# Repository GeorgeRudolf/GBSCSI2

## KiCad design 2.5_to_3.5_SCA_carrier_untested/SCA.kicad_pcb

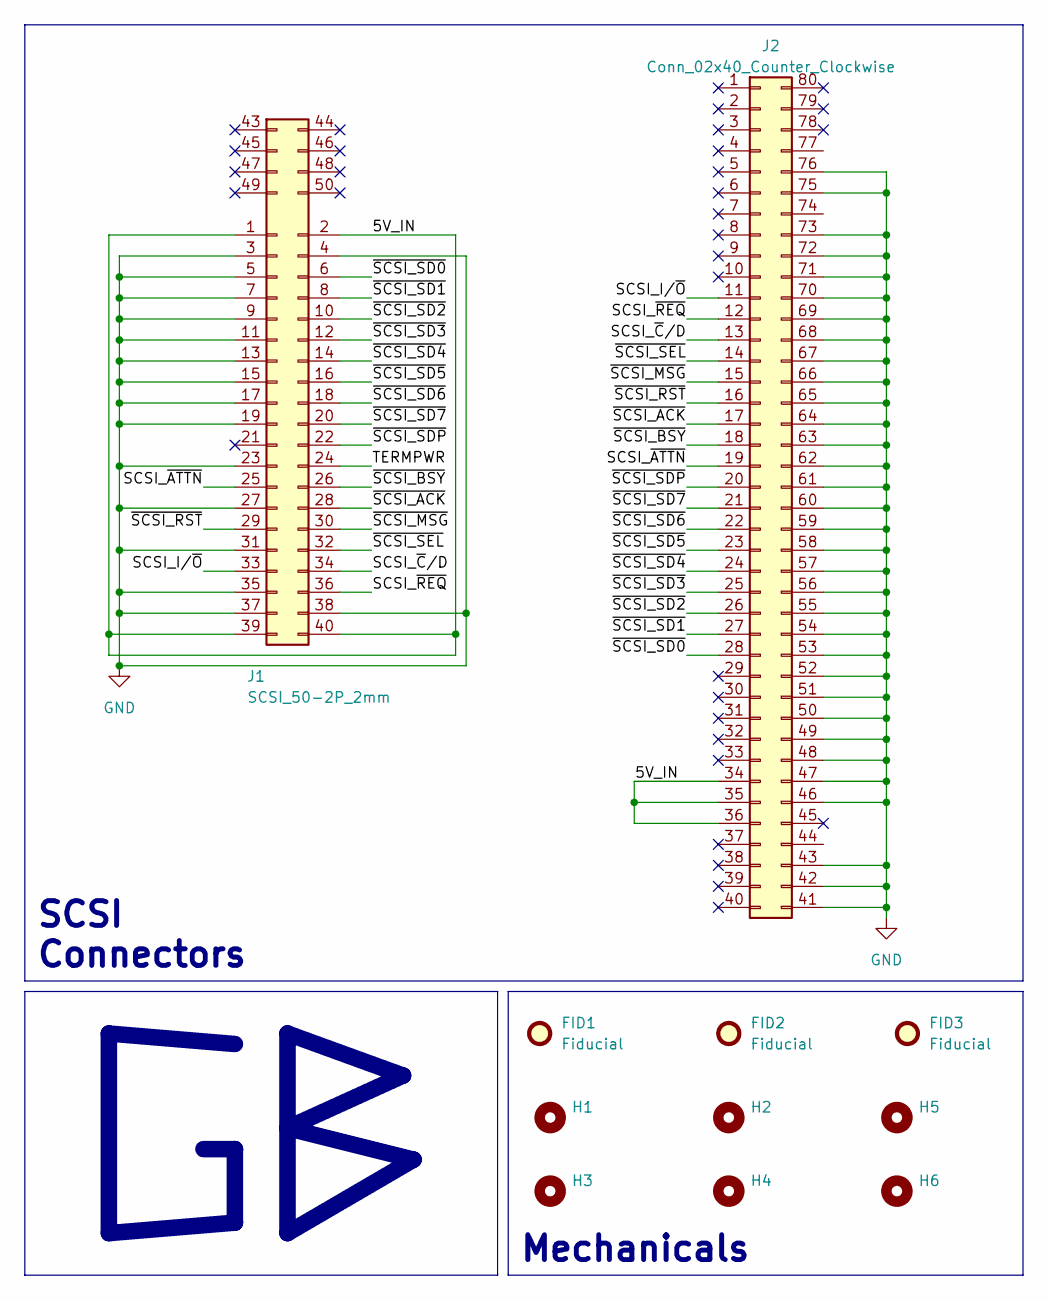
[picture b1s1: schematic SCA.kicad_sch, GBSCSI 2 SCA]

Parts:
FID1, FID2, FID3: Fiducial; Fiducial_0.5mm_Mask1mm; LCSC N/A
H1, H2, H3, H4, H5, H6: MH2.5_NPTH; LCSC N/A
J1: SCSI_50-2P_2mm; PinSocket_2x20_P2.00mm_Horizontal; LCSC N/A
J2: Conn_02x40_Counter_Clockwise; CHAMPII_80

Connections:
/5V_IN: J1.1, J1.2, J1.39, J1.40, J2.34, J2.35, J2.36
/SCSI_I/~O: J1.33, J2.11
/SCSI_~ATTN: J1.25, J2.19
/SCSI_~C/D: J1.34, J2.13
/SCSI_~REQ: J1.36, J2.12
/TERMPWR: J1.24
/~SCSI_ACK: J1.28, J2.17
/~SCSI_BSY: J1.26, J2.18
/~SCSI_MSG: J1.30, J2.15
/~SCSI_RST: J1.29, J2.16
/~SCSI_SD0: J1.6, J2.28
/~SCSI_SD1: J1.8, J2.27
/~SCSI_SD2: J1.10, J2.26
/~SCSI_SD3: J1.12, J2.25
/~SCSI_SD4: J1.14, J2.24
/~SCSI_SD5: J1.16, J2.23
/~SCSI_SD6: J1.18, J2.22
/~SCSI_SD7: J1.20, J2.21
/~SCSI_SDP: J1.22, J2.20
/~SCSI_SEL: J1.32, J2.14
GND: J1.3, J1.4, J1.5, J1.7, J1.9, J1.11, J1.13, J1.15, J1.17, J1.19, J1.23, J1.27, J1.31, J1.35, J1.37, J1.38, J2.41, J2.42, J2.43, J2.46, J2.47, J2.48, J2.49, J2.50, J2.51, J2.52, J2.53, J2.54, J2.55, J2.56, J2.57, J2.58, J2.59, J2.60, J2.61, J2.62, J2.63, J2.64, J2.65, J2.66, J2.67, J2.68, J2.69, J2.70, J2.71, J2.72, J2.73, J2.75, J2.76

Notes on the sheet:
SCSI Connectors
Mechanicals

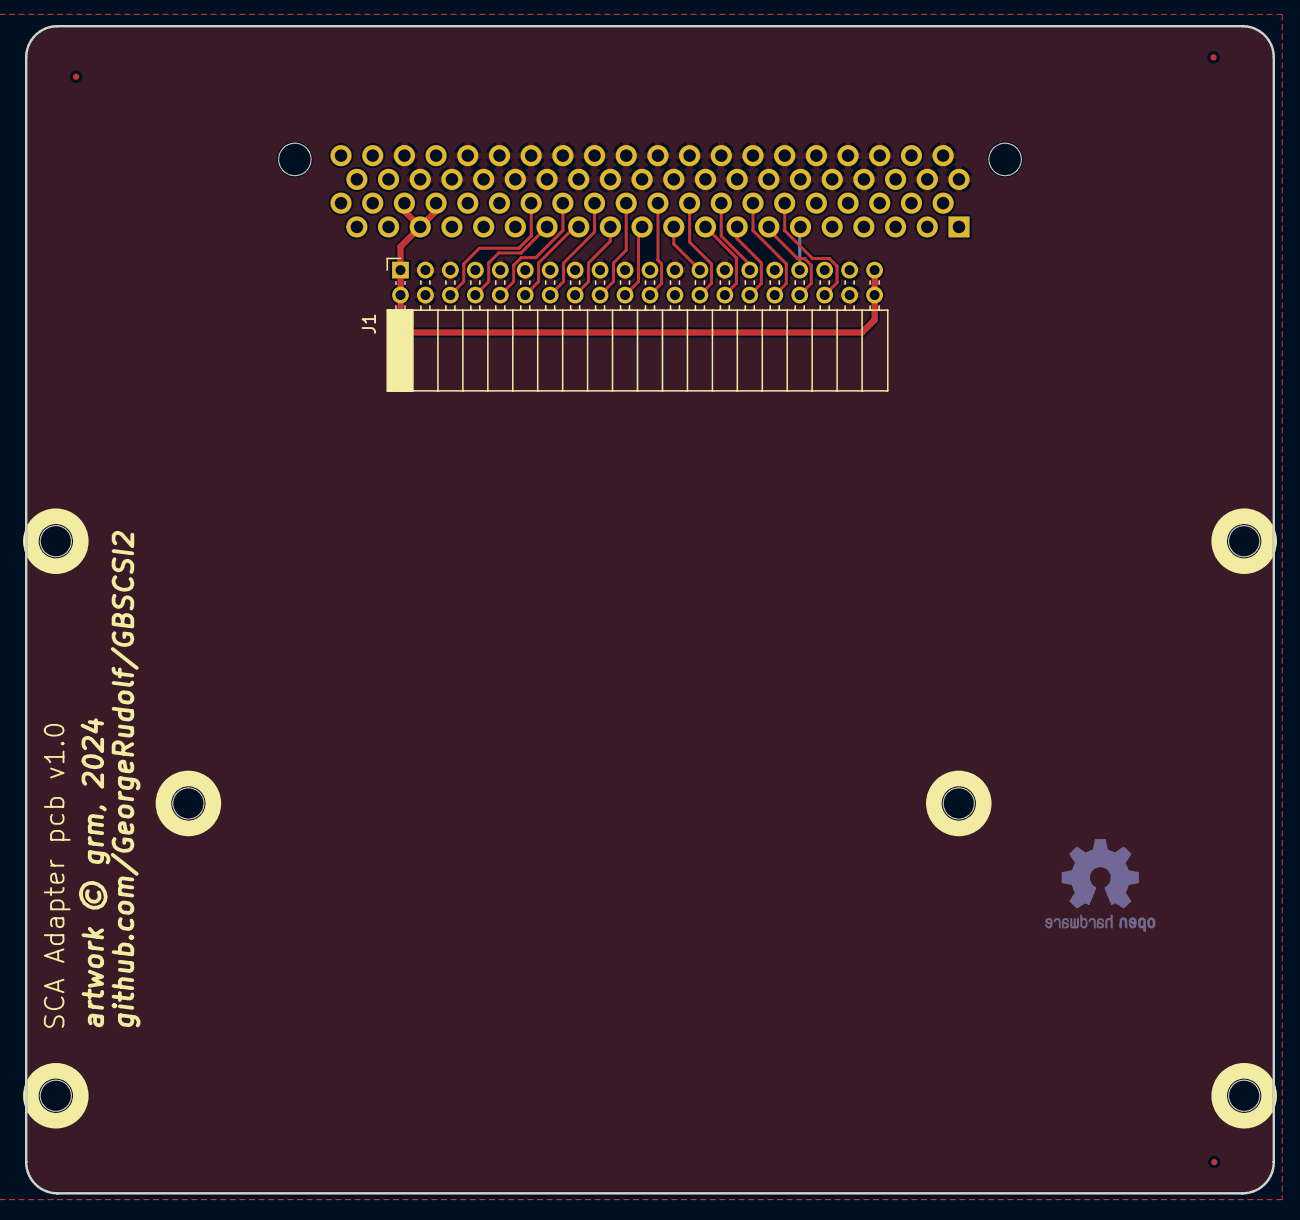
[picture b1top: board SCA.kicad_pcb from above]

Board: 4 copper layers, 100.0 x 93.5 mm, 11 parts (1 on the bottom side), 20 nets.

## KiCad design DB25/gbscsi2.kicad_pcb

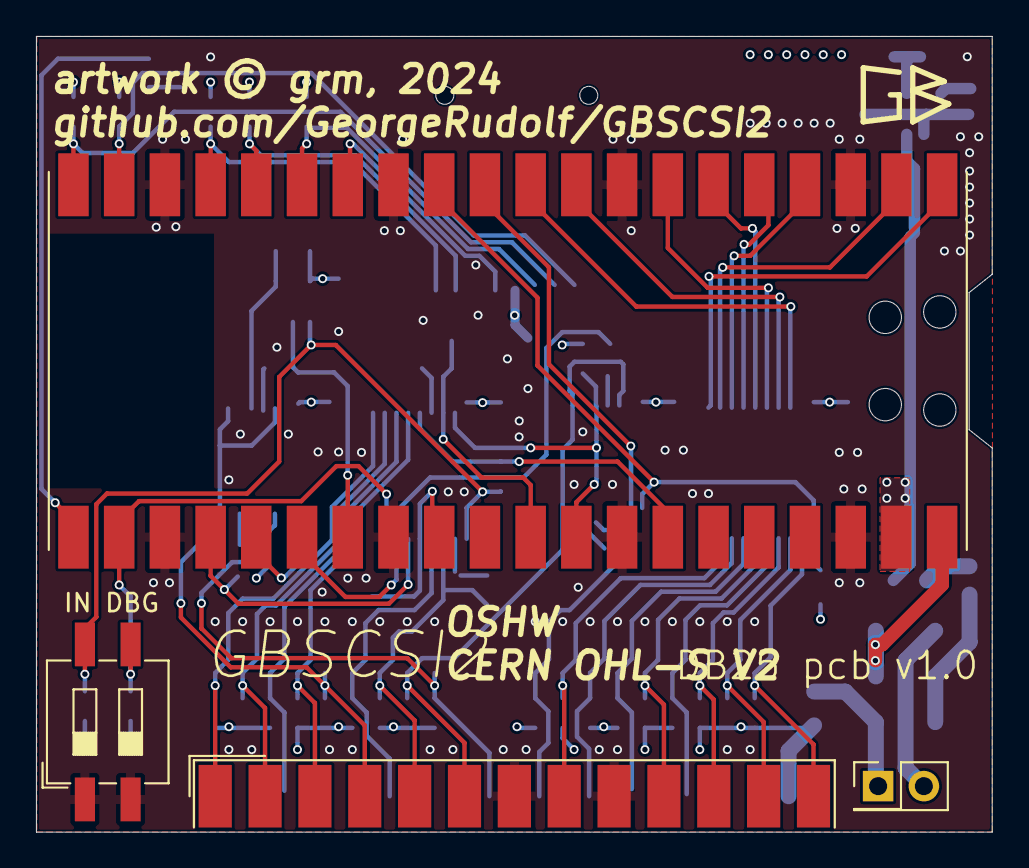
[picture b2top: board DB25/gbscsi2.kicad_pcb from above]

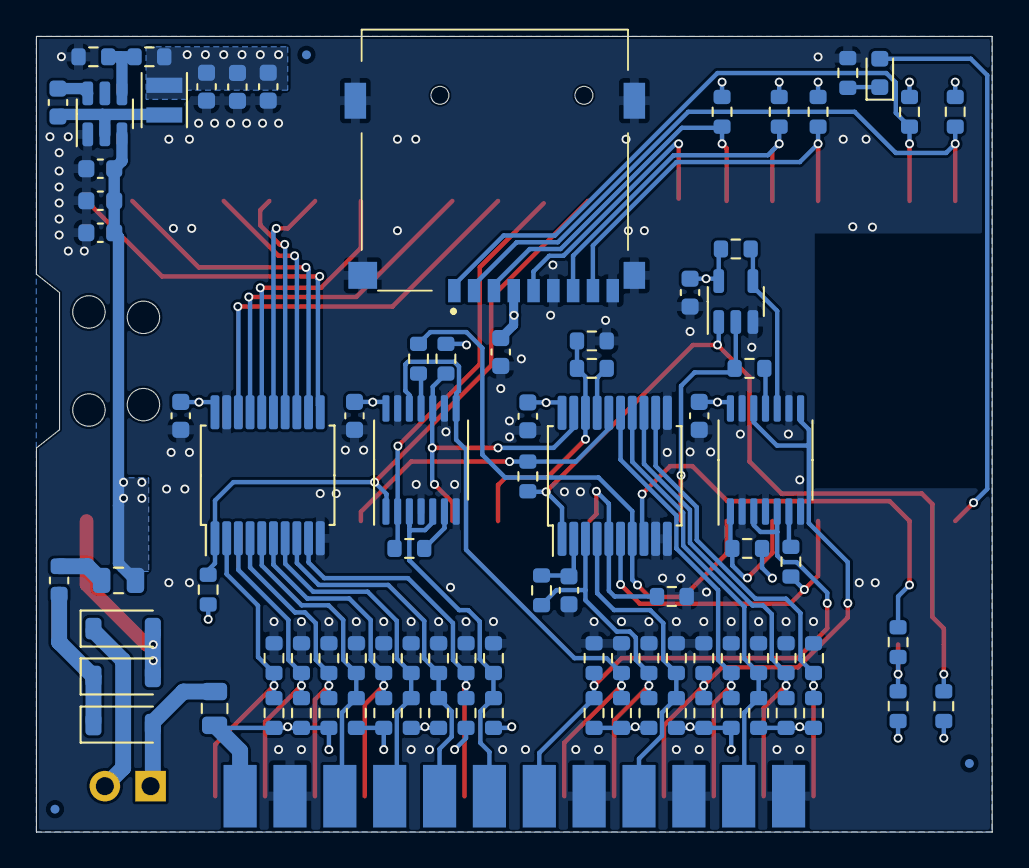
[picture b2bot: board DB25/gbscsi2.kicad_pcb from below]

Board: 4 copper layers, 53.1 x 44.2 mm, 96 parts (92 on the bottom side), 66 nets.

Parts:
C1, C3, C4, C5, C6, C7, C14, C16, C18: 100nF; C_0603_1608Metric
C2: 12pF; C_0603_1608Metric
C12, C13: 22uF; C_0603_1608Metric
C15: 10uF; C_0603_1608Metric
C17: 1uF; C_0603_1608Metric
D1: YELLOW; LED_0603_1608Metric
D2, D3, D4: D_Schottky; D_SOD-123
F1, F2: 1A; Fuse_0805_2012Metric
FID1, FID2, FID3: Fiducial; Fiducial_0.5mm_Mask1mm
J2: TF003; TF01A
J6: DB25_Plug; DSUB-25_Male_EdgeMount_P2.77mm
JP1: Jumper_2_Open; PinHeader_2x01_P2.54mm_Vertical
L1: Ferrite_Bead_Small; L_0603_1608Metric
L2: 2.2uH; L_Sunlord_SWPA252012S
R1, R2, R3, R5, R7, R8, R9, R10, R11, R12, R13, R18, R43: 4k7; R_0603_1608Metric
R4, R6, R15, R17, R19, R20, R21: 1k; R_0603_1608Metric
R14: 510; R_0603_1608Metric
R16: 110; R_0603_1608Metric
R22, R24, R26, R28, R30, R32, R34, R36, R38, R44, R45, R46, R47, R48, R49, R50, R51, R52: 220; R_0603_1608Metric
R23, R25, R27, R29, R31, R33, R35, R37, R39, R53, R54, R55, R56, R57, R58, R59, R60, R61: 330; R_0603_1608Metric
R41: 31k6; R_0603_1608Metric
R42: 10k; R_0603_1608Metric
SW1: SW_DIP_x02; SW_DIP_SPSTx02_Slide_6.7x6.64mm_W8.61mm_P2.54mm_LowProfile
U1: Pico W; RPi_Pico_W_SMD
U2, U3: 74LVT245; SSOP-20_5.3x7.2mm_P0.65mm
U4: 74AHCT1G125; SOT-23-5
U5, U6: 74LVT125; TSSOP-14_4.4x5mm_P0.65mm
U8: AP62250WU; TSOT-23-6

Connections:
+3V3: C1.1, C3.1, C4.1, C5.1, C6.1, C7.1, C12.1, C13.1, C16.1, J2.4 (VDD), L2.2, R1.2, R2.2, R3.2, R4.1, R5.2, R6.1, R7.2, R10.1, R11.1, R12.1, R13.1, R41.1, U2.20 (VCC), U3.20 (VCC), U4.5 (VCC), U5.14 (VCC), U6.14 (VCC)
+5V: C15.1, C17.1, C18.1, F2.2, U1.39 (VSYS), U8.3 (VIN)
/5V_TIE: D3.1 (K), D4.1 (K), L1.2
/ACTY: D1.1 (K), R14.2
/MCU_RST: R18.2, U1.27 (GPIO21), U4.2
/SCSI_I/~O: J6.3, R52.2, R61.1, U3.15 (B3)
/SCSI_~ATTN: J6.17, R44.2, R53.1, U3.4 (A2)
/SCSI_~C/D: J6.15, R50.2, R59.1, U3.14 (B4)
/SCSI_~REQ: J6.1, R51.2, R60.1, U3.12 (B6)
/SDIO_CLK: J2.5 (CLK), U1.14 (GPIO10)
/SDIO_CMD: J2.3 (CMD/DI), R3.1, U1.15 (GPIO11)
/SDIO_D0: J2.7 (DAT0/DO), R5.1, U1.16 (GPIO12)
/SDIO_D1: J2.8 (DAT1/NC), R7.1, U1.17 (GPIO13)
/SDIO_D2: J2.1 (DAT2/NC), R1.1, U1.19 (GPIO14)
/SDIO_D3: J2.2 (DAT3/CS), R2.1, U1.20 (GPIO15)
/TERMPWR: F1.1, J6.25, R22.1, R24.1, R26.1, R28.1, R30.1, R32.1, R34.1, R36.1, R38.1, R44.1, R45.1, R46.1, R47.1, R48.1, R49.1, R50.1, R51.1, R52.1
/VBUS: D2.2 (A), D3.2 (A), U1.40 (VBUS)
/~BUS_DIR: R10.2, U1.12 (GPIO9), U2.1 (A->B), U5.1
/~DEBUG: R6.2, R9.1, SW1.3
/~INITIATOR: R4.2, R8.1, SW1.4, U3.1 (A->B), U4.1
/~MCU_ACK: R15.1, R17.2, U1.31 (GPIO26_ADC0), U3.18 (B0)
/~MCU_ATTN: R8.2, U1.34 (GPIO28_ADC2), U3.16 (B2)
/~MCU_BSY_OUT: R11.2, U1.32 (GPIO27_ADC1), U3.19 (CE), U5.10
/~MCU_CD/SEL_IN: R20.1, U1.24 (GPIO18), U3.6 (A4)
/~MCU_IO: R43.2, U1.29 (GPIO22), U3.5 (A3)
/~MCU_MSG/BSY_IN: R21.1, U1.26 (GPIO20), U3.7 (A5)
/~MCU_REQ: R9.2, U1.22 (GPIO17), U3.8 (A6)
/~MCU_SD0: U1.1 (GPIO0), U2.11 (B7)
/~MCU_SD1: U1.2 (GPIO1), U2.12 (B6)
/~MCU_SD2: U1.4 (GPIO2), U2.13 (B5)
/~MCU_SD3: U1.5 (GPIO3), U2.14 (B4)
/~MCU_SD4: U1.6 (GPIO4), U2.15 (B3)
/~MCU_SD5: U1.7 (GPIO5), U2.16 (B2)
/~MCU_SD6: U1.9 (GPIO6), U2.17 (B1)
/~MCU_SD7: U1.10 (GPIO7), U2.18 (B0)
/~MCU_SDP: R19.2, U1.11 (GPIO8), U5.2
/~MCU_SEL_OUT: R13.2, U1.25 (GPIO19), U6.1
/~RST_OUT: R12.2, U4.4, U6.10
/~SCSI_ACK: J6.5, R16.1, R46.2, R55.1, U3.3 (A1)
/~SCSI_BSY: J6.6, R45.2, R54.1, U5.8, U5.12
/~SCSI_MSG: J6.2, R48.2, R57.1, U3.13 (B5)
/~SCSI_RST: J6.4, R47.2, R56.1, U6.8, U6.12
/~SCSI_SD0: J6.8, R22.2, R23.1, U2.9 (A7)
/~SCSI_SD1: J6.21, R24.2, R25.1, U2.8 (A6)
/~SCSI_SD2: J6.22, R26.2, R27.1, U2.7 (A5)
/~SCSI_SD3: J6.10, R28.2, R29.1, U2.6 (A4)
/~SCSI_SD4: J6.23, R30.2, R31.1, U2.5 (A3)
/~SCSI_SD5: J6.11, R32.2, R33.1, U2.4 (A2)
/~SCSI_SD6: J6.12, R34.2, R35.1, U2.3 (A1)
/~SCSI_SD7: J6.13, R36.2, R37.1, U2.2 (A0)
/~SCSI_SDP: J6.20, R38.2, R39.1, U5.3, U5.5
/~SCSI_SEL: J6.19, R49.2, R58.1, U6.3, U6.5
GND: C1.2, C2.2, C3.2, C4.2, C5.2, C6.2, C7.2, C12.2, C13.2, C15.2, C16.2, C17.2, C18.2, J2.6 (GND), J2.CD1, J2.MP1, J2.MP2, J2.MP3, J2.MP4, J6.7, J6.9, J6.14, J6.16, J6.18, J6.24, R14.1, R15.2, R23.2, R25.2, R27.2, R29.2, R31.2, R33.2, R35.2, R37.2, R39.2, R42.2, R43.1, R53.2, R54.2, R55.2, R56.2, R57.2, R58.2, R59.2, R60.2, R61.2, SW1.1, SW1.2, U1.3 (GND), U1.8 (GND), U1.13 (GND), U1.18 (GND), U1.23 (GND), U1.28 (GND), U1.33 (AGND), U1.38 (GND), U2.10 (GND), U2.19 (CE), U3.9 (A7), U3.10 (GND), U3.11 (B7), U4.3 (GND), U5.4, U5.7 (GND), U5.9, U5.13, U6.2, U6.4, U6.7 (GND), U6.9, U6.13, U8.1 (GND)
unnamed: D1.2 (A), U1.21 (GPIO16)
unnamed: D2.1 (K), JP1.2 (B)
unnamed: D4.2 (A), F1.2, JP1.1 (A)
unnamed: F2.1, L1.1
unnamed: R18.1, U6.11
unnamed: R19.1, U5.6
unnamed: R20.2, U6.6
unnamed: R21.2, U5.11
unnamed: C2.1, R16.2, U3.2 (A0)
unnamed: R17.1, U3.17 (B1)
unnamed: C14.2, U8.6 (BST)
unnamed: R41.2, R42.1, U8.4 (FB)
unnamed: C14.1, L2.1, U8.2 (SW)

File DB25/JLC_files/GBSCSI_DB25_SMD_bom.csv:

Designator,Footprint,Quantity,Value,LCSC Part #
"C1, C14, C16, C18, C3, C4, C5, C6, C7",603,9,100nF,C14663
"C12, C13",603,2,22uF,C59461
C15,603,1,10uF,C96446
C17,603,1,1uF,C15849
C2,603,1,12pF,C38523
D1,603,1,YELLOW,C72038
"D2, D3, D4",D_SOD-123,3,D_Schottky,C82544 
"F1, F2",805,2,1A,C468888
J2,TF01A,1,TF003,C5155563 
J6,DSUB-25_Male_EdgeMount_P2.77mm,1,DB25_Plug,N/A
JP1,PinHeader_2x01_P2.54mm_Vertical,1,Jumper_2_Open,N/A
L1,603,1,Ferrite_Bead_Small,C1002
L2,L_Sunlord_SWPA252012S,1,2.2uH,C351245
"R1, R10, R11, R12, R13, R18, R2, R3, R43, R5, R7, R8, R9",603,13,4k7,C23162
R14,603,1,510,C23193
"R15, R17, R19, R20, R21, R4, R6",603,7,1k,C21190
R16,603,1,110,C22781
"R22, R24, R26, R28, R30, R32, R34, R36, R38, R44, R45, R46, R47, R48, R49, R50, R51, R52",603,18,220,C22962
"R23, R25, R27, R29, R31, R33, R35, R37, R39, R53, R54, R55, R56, R57, R58, R59, R60, R61",603,18,330,C23138
R41,603,1,31k6,C25967
R42,603,1,10k,C25804
SW1,SW_DIP_SPSTx02_Slide_6.7x6.64mm_W8.61mm_P2.54mm_LowProfile,1,SW_DIP_x02,N/A
U1,RPi_Pico_W_SMD,1,Pico W,C7203003
"U2, U3",SSOP-20_5.3x7.2mm_P0.65mm,2,74LVT245,C2652121
U4,SOT-23-5,1,74AHCT1G125,C12494
"U5, U6",TSSOP-14_4.4x5mm_P0.65mm,2,74LVT125,C7042
U8,TSOT-23-6,1,AP62250WU,C5184228

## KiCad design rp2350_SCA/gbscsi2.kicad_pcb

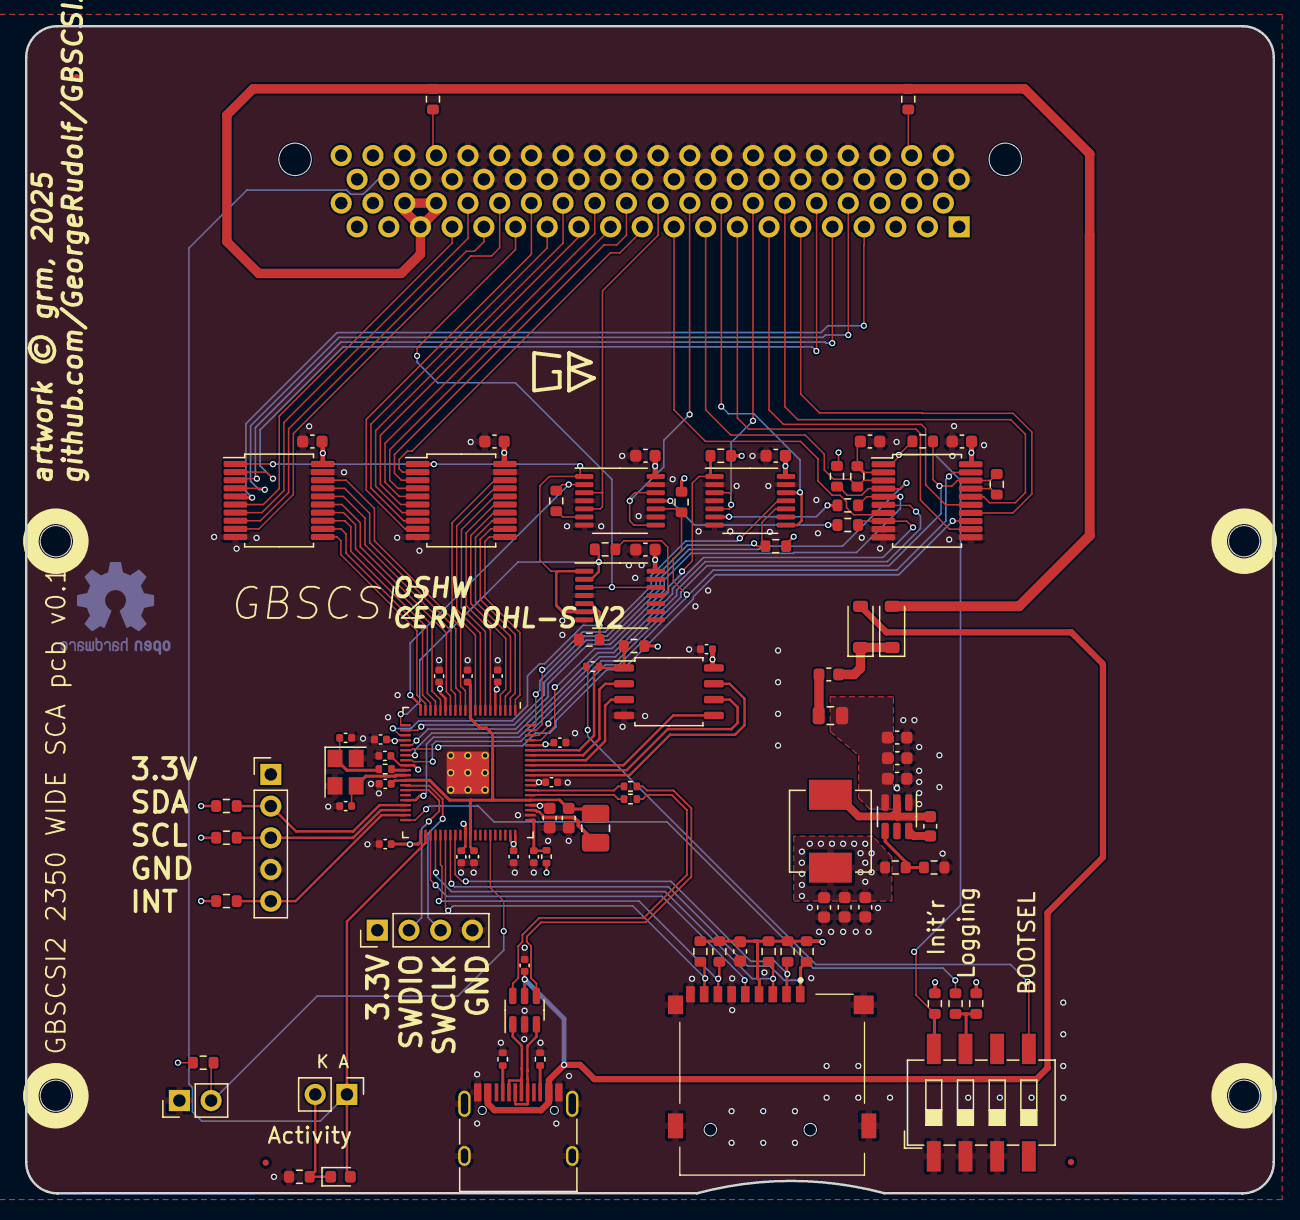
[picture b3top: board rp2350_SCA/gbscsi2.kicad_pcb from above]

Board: 4 copper layers, 100.0 x 93.6 mm, 104 parts (1 on the bottom side), 113 nets.

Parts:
C1, C3, C4, C5, C6, C7, C14, C16, C18, C37: 100nF; C_0603_1608Metric
C2: 12pF; C_0603_1608Metric
C12, C13: 22uF; C_0603_1608Metric
C15: 10uF; C_0603_1608Metric
C17: 1uF; C_0603_1608Metric
C20, C21: 22pF; C_0402_1005Metric
C22, C24, C27, C28, C29, C30, C31, C32, C33, C34, C38, C39: 100nF; C_0402_1005Metric
C23, C36: 4.7uF; C_0402_1005Metric
C25: 1uF; C_0402_1005Metric
C26, C35: 4.7uF; C_0603_1608Metric
D1: YELLOW; LED_0603_1608Metric
D3, D5: D_Schottky; D_SOD-123
F2: 1A; Fuse_0805_2012Metric
FID1, FID2, FID3: Fiducial; Fiducial_0.5mm_Mask1mm
H1, H2, H3, H4: MH2.5_NPTH
J1: USB_DATA; USB_C_Receptacle_HRO_TYPE-C-31-M-12
J2: TF003; TF01A
J3, J8: Conn_01x02; PinHeader_1x02_P2.54mm_Vertical
J6: Conn_01x05; PinHeader_1x05_P2.54mm_Vertical
J7: Conn_01x04; PinHeader_1x04_P2.54mm_Vertical
J9: Conn_02x40_Counter_Clockwise; CHAMPII_80
L1: Ferrite_Bead_Small; L_0603_1608Metric
L2: 2.2uH; L_Vishay_IHLP-2525
L3: 3.3uH; L_1008_2520Metric_Pad1.43x2.20mm_HandSolder
R1, R2, R3, R5, R7, R8, R9, R10, R11, R12, R13, R15, R40, R51, R52, R54, R66: 4k7; R_0603_1608Metric
R4, R6, R17, R19, R20, R21, R64: 1k; R_0603_1608Metric
R14, R53: 1k; R_0402_1005Metric
R16: 110; R_0603_1608Metric
R18, R42, R67: 10k; R_0603_1608Metric
R41: 31k6; R_0603_1608Metric
R46, R47: 5k1; R_0402_1005Metric
R48, R49, R65: 27; R_0402_1005Metric
R50: 510; R_0603_1608Metric
SW1: SW_DIP_x03; SW_DIP_SPSTx04_Slide_6.7x11.72mm_W8.61mm_P2.54mm_LowProfile
U1: RP2350_80QFN; RP2350-QFN-80-1EP_10x10_P0.4mm_EP3.4x3.4mm_ThermalVias
U2, U3, U11: 74LVT245; SSOP-20_5.3x7.2mm_P0.65mm
U4, U5, U6: 74LVT125; TSSOP-14_4.4x5mm_P0.65mm
U8: AP62250WU; TSOT-23-6
U9: USB TVS; SOT-23-6
U10: W25Q128JVS; SOIC-8_5.23x5.23mm_P1.27mm
Y1: 12MHz; Crystal_SMD_3225-4Pin_3.2x2.5mm

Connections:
+1V1: C22.1, C23.1, C24.1, C35.1, L3.1, U1.10 (DVDD), U1.32 (DVDD), U1.51 (DVDD), U1.65 (VREG_FB)
+3V3: C1.1, C3.1, C4.1, C5.1, C6.1, C7.1, C12.1, C13.1, C16.1, C25.1, C26.1, C27.1, C28.1, C29.1, C30.1, C31.1, C32.1, C34.1, C37.1, C38.1, C39.1, J2.4 (VDD), J6.1, J7.1, L2.2, R1.2, R2.2, R3.2, R4.1, R5.2, R6.1, R7.2, R11.1, R12.1, R13.1, R15.2, R40.1, R41.1, R51.2, R52.2, R54.2, R65.2, R66.1, U1.5 (IOVDD), U1.15 (IOVDD), U1.24 (IOVDD), U1.29 (IOVDD), U1.41 (IOVDD), U1.50 (IOVDD), U1.59 (ADC_AVDD), U1.60 (IOVDD), U1.64 (VREG_VIN), U1.68 (USB_OTP_VDD), U1.69 (QSPI_IOVDD), U1.76 (IOVDD), U2.20 (VCC), U3.20 (VCC), U4.14 (VCC), U5.14 (VCC), U6.14 (VCC), U10.8 (VCC), U11.20 (VCC)
+5V: C15.1, C17.1, C18.1, F2.2, U8.3 (VIN)
/5V_IN: D3.2 (A), J9.34, J9.35, J9.36, R18.2, R67.2
/5V_TIE: D3.1 (K), D5.1 (K), L1.2
/ACTY: D1.2 (A), J3.1, J9.77, U1.42 (GPIO33)
/ACTY_RTN: D1.1 (K), J3.2, R50.2
/BUS_DIR: R10.2, U1.23 (GPIO23), U4.5
/CC1: J1.A5 (CC1), R47.1
/CC2: J1.B5 (CC2), R46.1
/Din+: J1.A6 (D1+), J1.B6 (D2+), U9.3 (I/O2)
/Din-: J1.A7 (D1-), J1.B7 (D2-), U9.1 (I/O1)
/Dout+: R48.1, U9.4 (I/O2)
/Dout-: R49.1, U9.6 (I/O1)
/EJECT: J8.2, R66.2, U1.55 (GPIO44_ADC4)
/I²C_INT: J6.5, R52.1, U1.39 (GPIO31)
/I²C_SCL: J6.3, R51.1, U1.38 (GPIO30)
/I²C_SDA: J6.2, R15.1, U1.37 (GPIO29)
/QSPI_SCLK: U1.71 (QSPI_SCLK), U10.6 (CLK)
/QSPI_SD0: U1.72 (QSPI_SD0), U10.5 (DI(IO0))
/QSPI_SD1: U1.74 (QSPI_SD1), U10.2 (DO(IO1))
/QSPI_SD2: U1.73 (QSPI_SD2), U10.3 (IO2)
/QSPI_SD3: U1.70 (QSPI_SD3), U10.7 (IO3)
/QSPI_SS: R53.1, R54.1, U1.75 (QSPI_SS), U10.1 (~CS)
/SCSI_I/~O: J9.11, U3.14 (B4)
/SCSI_~ATTN: J9.19, U3.7 (A5)
/SCSI_~C/D: J9.13, U3.15 (B3)
/SCSI_~REQ: J9.12, U3.16 (B2)
/SDIO_CLK: J2.5 (CLK), U1.43 (GPIO34)
/SDIO_CMD: J2.3 (CMD/DI), R3.1, U1.44 (GPIO35)
/SDIO_D0: J2.7 (DAT0/DO), R5.1, U1.45 (GPIO36)
/SDIO_D1: J2.8 (DAT1/NC), R7.1, U1.46 (GPIO37)
/SDIO_D2: J2.1 (DAT2/NC), R1.1, U1.47 (GPIO38)
/SDIO_D3: J2.2 (DAT3/CS), R2.1, U1.48 (GPIO39)
/SWCLK: J7.3, U1.33 (SWCLK)
/SWD: J7.2, U1.34 (SWDIO)
/USB_D+: R48.2, U1.67 (USB_DP)
/USB_D-: R49.2, U1.66 (USB_DM)
/VBUS: C33.1, D5.2 (A), J1.A4 (VBUS), J1.A9 (VBUS), J1.B4 (VBUS), J1.B9 (VBUS), U9.5 (VBUS)
/VREG_LX: L3.2, U1.63 (VREG_LX)
/XIN: R14.1, U1.30 (XIN)
/XOUT: C20.1, U1.31 (XOUT), Y1.3
/~BUS_DIR: U2.1 (A->B), U4.1, U4.6, U5.1, U11.1 (A->B)
/~DEBUG: R9.2, U1.40 (GPIO32)
/~INITIATOR: R4.2, R8.1, SW1.6, U3.1 (A->B)
/~MCU_ACK: R8.2, R17.2, U1.28 (GPIO27), U3.18 (B0)
/~MCU_ATTN: U1.26 (GPIO25), U3.13 (B5)
/~MCU_BSY_OUT: R11.2, U1.78 (GPIO1), U3.19 (CE), U5.10
/~MCU_CD/SEL_IN: R20.1, U1.25 (GPIO24), U3.5 (A3)
/~MCU_IO: U1.36 (GPIO28), U3.6 (A4)
/~MCU_MSG/BSY_IN: R21.1, U1.27 (GPIO26), U3.8 (A6)
/~MCU_REQ: R40.2, U1.22 (GPIO22), U3.4 (A2)
/~MCU_RST_IN: U1.79 (GPIO2), U6.11
/~MCU_RST_OUT: R12.2, U1.80 (GPIO3), U6.10
/~MCU_SD0: U1.1 (GPIO4), U2.11 (B7)
/~MCU_SD1: U1.2 (GPIO5), U2.12 (B6)
/~MCU_SD2: U1.3 (GPIO6), U2.13 (B5)
/~MCU_SD3: U1.4 (GPIO7), U2.14 (B4)
/~MCU_SD4: U1.6 (GPIO8), U2.15 (B3)
/~MCU_SD5: U1.7 (GPIO9), U2.16 (B2)
/~MCU_SD6: U1.8 (GPIO10), U2.17 (B1)
/~MCU_SD7: U1.9 (GPIO11), U2.18 (B0)
/~MCU_SD8: U1.11 (GPIO12), U11.18 (B0)
/~MCU_SD9: U1.12 (GPIO13), U11.17 (B1)
/~MCU_SD10: U1.13 (GPIO14), U11.16 (B2)
/~MCU_SD11: U1.14 (GPIO15), U11.15 (B3)
/~MCU_SD12: U1.16 (GPIO16), U11.14 (B4)
/~MCU_SD13: U1.17 (GPIO17), U11.13 (B5)
/~MCU_SD14: U1.18 (GPIO18), U11.12 (B6)
/~MCU_SD15: U1.19 (GPIO19), U11.11 (B7)
/~MCU_SDP1: R64.2, U1.21 (GPIO21), U4.2
/~MCU_SDP: R19.2, U1.20 (GPIO20), U5.2
/~MCU_SEL_OUT: R13.2, U1.77 (GPIO0), U6.1
/~SCSI_ACK: J9.17, R16.1, U3.3 (A1)
/~SCSI_BSY: J9.18, U5.8, U5.12
/~SCSI_MSG: J9.15, U3.12 (B6)
/~SCSI_RST: J9.16, U6.8, U6.12
/~SCSI_SD0: J9.28, U2.9 (A7)
/~SCSI_SD1: J9.27, U2.8 (A6)
/~SCSI_SD2: J9.26, U2.7 (A5)
/~SCSI_SD3: J9.25, U2.6 (A4)
/~SCSI_SD4: J9.24, U2.5 (A3)
/~SCSI_SD5: J9.23, U2.4 (A2)
/~SCSI_SD6: J9.22, U2.3 (A1)
/~SCSI_SD7: J9.21, U2.2 (A0)
/~SCSI_SD8: J9.10, U11.2 (A0)
/~SCSI_SD9: J9.9, U11.3 (A1)
/~SCSI_SD10: J9.8, U11.4 (A2)
/~SCSI_SD11: J9.7, U11.5 (A3)
/~SCSI_SD12: J9.33, U11.6 (A4)
/~SCSI_SD13: J9.32, U11.7 (A5)
/~SCSI_SD14: J9.31, U11.8 (A6)
/~SCSI_SD15: J9.30, U11.9 (A7)
/~SCSI_SDP1: J9.29, U4.3, U4.12
/~SCSI_SDP: J9.20, U5.3, U5.5
/~SCSI_SEL: J9.14, U6.3, U6.5
/~USB_BOOT: R53.2, SW1.4
GND: C1.2, C2.2, C3.2, C4.2, C5.2, C6.2, C7.2, C12.2, C13.2, C15.2, C16.2, C17.2, C18.2, C20.2, C21.2, C22.2, C23.2, C24.2, C25.2, C26.2, C27.2, C28.2, C29.2, C30.2, C31.2, C32.2, C33.2, C34.2, C35.2, C36.2, C37.2, C38.2, C39.2, J1.A1 (GND), J1.A12 (GND), J1.B1 (GND), J1.B12 (GND), J1.S1 (SHIELD), J2.6 (GND), J2.CD1, J2.MP1, J2.MP2, J2.MP3, J2.MP4, J6.4, J7.4, J8.1, J9.41, J9.42, J9.43, J9.46, J9.47, J9.48, J9.49, J9.50, J9.51, J9.52, J9.53, J9.54, J9.55, J9.56, J9.57, J9.58, J9.59, J9.60, J9.61, J9.62, J9.63, J9.64, J9.65, J9.66, J9.67, J9.68, J9.69, J9.70, J9.71, J9.72, J9.73, J9.75, J9.76, R10.1, R42.2, R46.2, R47.2, R50.1, SW1.1, SW1.2, SW1.3, U1.62 (VREG_PGND), U1.81 (GND), U2.10 (GND), U2.19 (CE), U3.9 (A7), U3.10 (GND), U3.11 (B7), U4.4, U4.7 (GND), U4.13, U5.4, U5.7 (GND), U5.9, U5.13, U6.2, U6.4, U6.7 (GND), U6.9, U6.13, U8.1 (GND), U9.2 (GND), U10.4 (GND), U11.10 (GND), U11.19 (CE), Y1.2, Y1.4
unnamed: C21.1, R14.2, Y1.1
unnamed: F2.1, L1.1
unnamed: J9.44, R67.1
unnamed: J9.74, R18.1
unnamed: R6.2, R9.1, SW1.5
unnamed: R19.1, U5.6
unnamed: R20.2, U6.6
unnamed: R21.2, U5.11
unnamed: R64.1, U4.11
unnamed: C36.1, R65.1, U1.61 (VREG_AVDD)
unnamed: C2.1, R16.2, U3.2 (A0)
unnamed: R17.1, U3.17 (B1)
unnamed: C14.2, U8.6 (BST)
unnamed: R41.2, R42.1, U8.4 (FB)
unnamed: C14.1, L2.1, U8.2 (SW)

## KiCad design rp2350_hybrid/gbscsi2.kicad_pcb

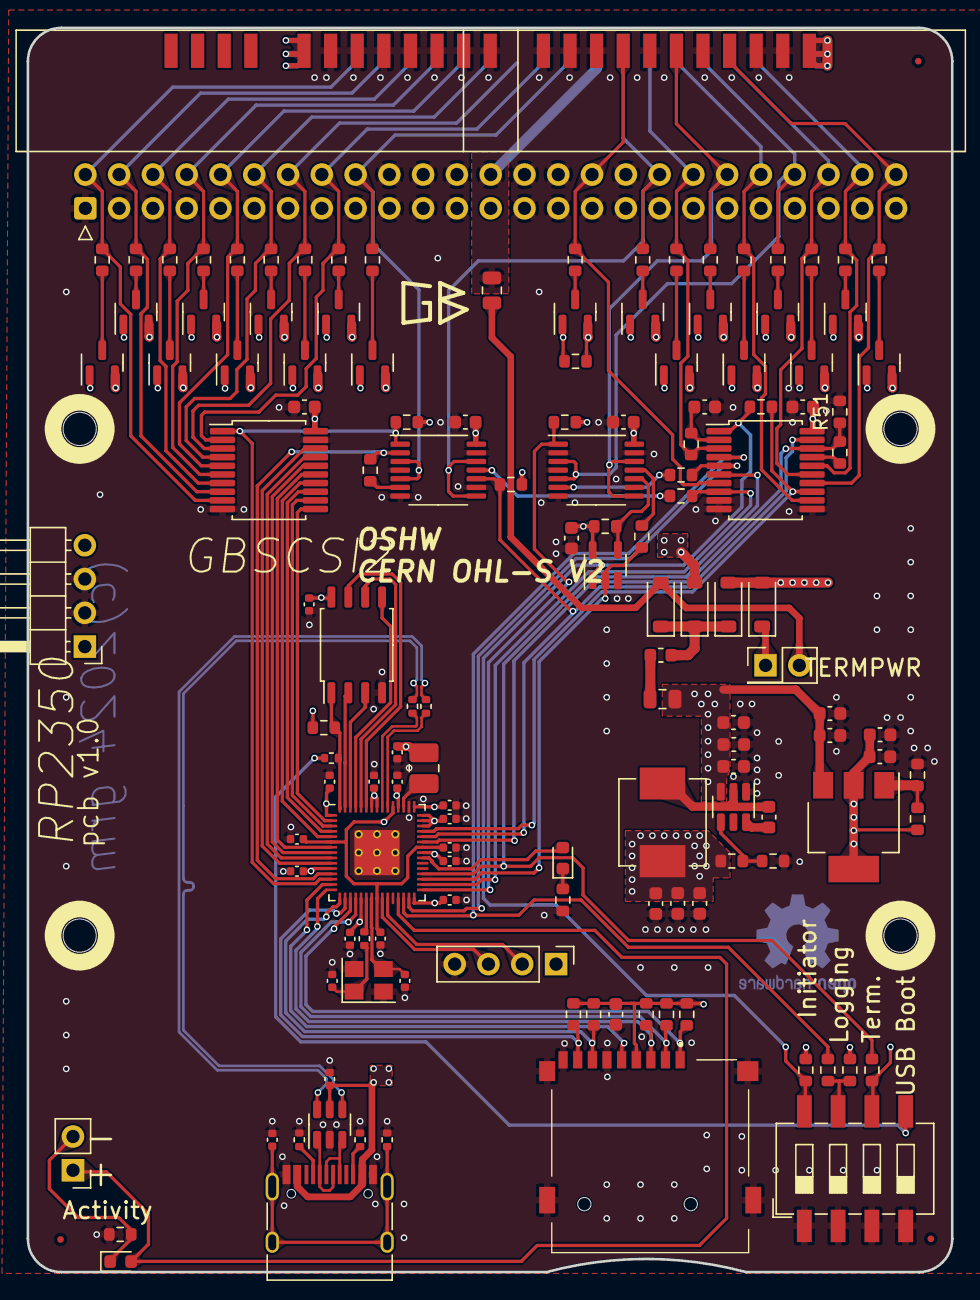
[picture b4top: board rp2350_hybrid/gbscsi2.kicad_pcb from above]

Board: 4 copper layers, 69.5 x 93.5 mm, 146 parts (0 on the bottom side), 113 nets.

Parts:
C1, C3, C4, C5, C6, C7, C10, C11, C14, C16, C18: 100nF; C_0603_1608Metric
C2: 12pF; C_0603_1608Metric
C8, C9, C17: 1uF; C_0603_1608Metric
C12, C13: 22uF; C_0603_1608Metric
C15: 10uF; C_0603_1608Metric
C19: 4.7nF; C_0402_1005Metric
C20, C21: 22pF; C_0402_1005Metric
C22, C24, C27, C28, C29, C30, C31, C32, C33, C34: 100nF; C_0402_1005Metric
C23, C25: 1uF; C_0402_1005Metric
C26, C35: 4.7uF; C_0402_1005Metric
C36: 100n; C_0402_1005Metric
D1, D6: YELLOW; LED_0603_1608Metric
D2, D3, D4, D5: D_Schottky; D_SOD-123
F1, F2: 1A; Fuse_0805_2012Metric
FID1, FID2, FID3: Fiducial; Fiducial_0.5mm_Mask1mm
H1, H2, H3, H4: MH2.5_NPTH
J1: USB_DATA; USB_C_Receptacle_HRO_TYPE-C-31-M-12
J2: TF003; TF01A
J3: Conn_01x02; PinHeader_1x02_P2.54mm_Vertical
J4: Conn_01x04; PinHeader_1x04_P2.54mm_Horizontal
J5: SCSI_50-2P_2mm; PinHeader_2x25-2_P2.00mm_straddle
J6: SCSI_50P_2.54mm; IDC-Header_2x25_P2.54mm_Horizontal
J7: Conn_01x04; PinHeader_1x04_P2.54mm_Vertical
JP3: Jumper_2_Open; PinHeader_2x01_P2.54mm_Vertical
L1: Ferrite_Bead_Small; L_0603_1608Metric
L2: 2.2uH; L_Vishay_IHLP-2525
L3: 3.3uH; L_1008_2520Metric_Pad1.43x2.20mm_HandSolder
Q1, Q2, Q3, Q4, Q5, Q6, Q7, Q8, Q9, Q10, Q11, Q12, Q13, Q14, Q15, Q16, Q17, Q18: AO3401A; SOT-23
R1, R2, R3, R5, R7, R8, R9, R10, R11, R12, R13, R18, R40, R43, R54: 4k7; R_0603_1608Metric
R4, R6, R17, R19, R20, R21, R51: 1k; R_0603_1608Metric
R14, R53: 1k; R_0402_1005Metric
R15: 1M; R_0402_1005Metric
R16, R22, R23, R24, R25, R26, R27, R28, R29, R30, R31, R32, R33, R34, R35, R36, R37, R38, R39: 110; R_0603_1608Metric
R41: 31k6; R_0603_1608Metric
R42: 10k; R_0603_1608Metric
R44: R_0603_1608Metric
R45: 0; R_0603_1608Metric
R46, R47: 5k1; R_0402_1005Metric
R48, R49: 27; R_0402_1005Metric
R50, R52: 510; R_0603_1608Metric
SW1: SW_DIP_x04; SW_DIP_SPSTx04_Slide_6.7x11.72mm_W8.61mm_P2.54mm_LowProfile
U1: RP2350_60QFN; RP2350-QFN-60-1EP_7x7_P0.4mm_EP3.4x3.4mm_ThermalVias
U2, U3: 74LVT245; SSOP-20_5.3x7.2mm_P0.65mm
U4: 74AHCT1G125; SOT-23-5
U5, U6: 74LVT125; TSSOP-14_4.4x5mm_P0.65mm
U7: AZ1117-2.85; SOT-223-3_TabPin2
U8: AP62250WU; TSOT-23-6
U9: USB TVS; SOT-23-6
U10: W25Q128JVS; SOIC-8_5.23x5.23mm_P1.27mm
Y1: 12MHz; Crystal_SMD_3225-4Pin_3.2x2.5mm

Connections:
+1V1: C22.1, C23.1, C24.1, C35.1, L3.1, U1.6 (DVDD), U1.23 (DVDD), U1.39 (DVDD), U1.50 (VREG_FB)
+2V8: C9.1, C11.1, Q1.2 (S), Q2.2 (S), Q3.2 (S), Q4.2 (S), Q5.2 (S), Q6.2 (S), Q7.2 (S), Q8.2 (S), Q9.2 (S), Q10.2 (S), Q11.2 (S), Q12.2 (S), Q13.2 (S), Q14.2 (S), Q15.2 (S), Q16.2 (S), Q17.2 (S), Q18.2 (S), R40.1, R44.2, U7.2 (VO)
+3V3: C1.1, C3.1, C4.1, C5.1, C6.1, C7.1, C12.1, C13.1, C16.1, C25.1, C26.1, C27.1, C28.1, C29.1, C30.1, C31.1, C32.1, C34.1, C36.1, J2.4 (VDD), J7.1, L2.2, R1.2, R2.2, R3.2, R4.1, R5.2, R6.1, R7.2, R10.1, R11.1, R12.1, R13.1, R41.1, R54.2, U1.1 (IOVDD), U1.11 (IOVDD), U1.20 (IOVDD), U1.30 (IOVDD), U1.38 (IOVDD), U1.43 (GPIO29_ADC3), U1.44 (ADC_AVDD), U1.45 (IOVDD), U1.46 (VREG_AVDD), U1.49 (VREG_VIN), U1.53 (USB_OTP_VDD), U1.54 (QSPI_IOVDD), U2.20 (VCC), U3.20 (VCC), U4.5 (VCC), U5.14 (VCC), U6.14 (VCC), U10.8 (VCC)
+5V: C8.1, C10.1, C15.1, C17.1, C18.1, F2.2, U7.3 (VI), U8.3 (VIN)
/5V_IN: D2.2 (A), D3.2 (A), J4.1, J5.1, J5.2, J5.39, J5.40
/5V_TIE: D3.1 (K), D4.1 (K), D5.1 (K), L1.2
/ACTY: D1.1 (K), J3.2, R50.2
/CC1: J1.A5 (CC1), R47.1
/CC2: J1.B5 (CC2), R46.1
/Din+: J1.A6 (D1+), J1.B6 (D2+), U9.3 (I/O2)
/Din-: J1.A7 (D1-), J1.B7 (D2-), U9.1 (I/O1)
/Dout+: R48.1, U9.4 (I/O2)
/Dout-: R49.1, U9.6 (I/O1)
/GPIO16: D1.2 (A), J3.1, U1.27 (GPIO16)
/MCU_RST: R18.2, U1.33 (GPIO21), U4.2
/QSPI_SCLK: U1.56 (QSPI_SCLK), U10.6 (CLK)
/QSPI_SD0: U1.57 (QSPI_SD0), U10.5 (DI(IO0))
/QSPI_SD1: U1.59 (QSPI_SD1), U10.2 (DO(IO1))
/QSPI_SD2: U1.58 (QSPI_SD2), U10.3 (IO2)
/QSPI_SD3: U1.55 (QSPI_SD3), U10.7 (IO3)
/QSPI_SS: R53.1, R54.1, U1.60 (QSPI_SS), U10.1 (~CS)
/SCSI_I/~O: J5.33, J6.50, R39.1, U3.14 (B4)
/SCSI_~ATTN: J5.25, J6.32, R31.1, U3.7 (A5)
/SCSI_~C/D: J5.34, J6.46, R37.1, U3.15 (B3)
/SCSI_~REQ: J5.36, J6.48, R38.1, U3.16 (B2)
/SDIO_CLK: J2.5 (CLK), U1.14 (GPIO10)
/SDIO_CMD: J2.3 (CMD/DI), R3.1, U1.15 (GPIO11)
/SDIO_D0: J2.7 (DAT0/DO), R5.1, U1.16 (GPIO12)
/SDIO_D1: J2.8 (DAT1/NC), R7.1, U1.17 (GPIO13)
/SDIO_D2: J2.1 (DAT2/NC), R1.1, U1.18 (GPIO14)
/SDIO_D3: J2.2 (DAT3/CS), R2.1, U1.19 (GPIO15)
/SWCLK: J7.3, U1.24 (SWCLK)
/SWD: J7.2, U1.25 (SWD)
/TERMPWR: F1.1, J5.24, J6.26
/USB_D+: R48.2, U1.52 (USB_DP)
/USB_D-: R49.2, U1.51 (USB_DM)
/VBUS: C33.1, D5.2 (A), J1.A4 (VBUS), J1.A9 (VBUS), J1.B4 (VBUS), J1.B9 (VBUS), U9.5 (VBUS)
/VREG_LX: L3.2, U1.48 (VREG_LX)
/XIN: R14.1, U1.21 (XIN)
/XOUT: C20.1, U1.22 (XOUT), Y1.3
/~BUS_DIR: R10.2, U1.13 (GPIO9), U2.1 (A->B), U5.1
/~DEBUG: R6.2, R9.1, SW1.7
/~INITIATOR: R4.2, R8.1, SW1.8, U3.1 (A->B), U4.1
/~MCU_ACK: R17.2, R51.1, U1.40 (GPIO26_ADC0), U3.18 (B0)
/~MCU_ATTN: R8.2, U1.42 (GPIO28_ADC2), U3.13 (B5)
/~MCU_BSY_OUT: R11.2, U1.41 (GPIO27_ADC1), U3.19 (CE), U5.10
/~MCU_CD/SEL_IN: R20.1, U1.29 (GPIO18), U3.5 (A3)
/~MCU_IO: R43.2, U1.34 (GPIO22), U3.6 (A4)
/~MCU_MSG/BSY_IN: R21.1, U1.32 (GPIO20), U3.8 (A6)
/~MCU_REQ: R9.2, U1.28 (GPIO17), U3.4 (A2)
/~MCU_SD0: U1.2 (GPIO0), U2.11 (B7)
/~MCU_SD1: U1.3 (GPIO1), U2.12 (B6)
/~MCU_SD2: U1.4 (GPIO2), U2.13 (B5)
/~MCU_SD3: U1.5 (GPIO3), U2.14 (B4)
/~MCU_SD4: U1.7 (GPIO4), U2.15 (B3)
/~MCU_SD5: U1.8 (GPIO5), U2.16 (B2)
/~MCU_SD6: U1.9 (GPIO6), U2.17 (B1)
/~MCU_SD7: U1.10 (GPIO7), U2.18 (B0)
/~MCU_SDP: R19.2, U1.12 (GPIO8), U5.2
/~MCU_SEL_OUT: R13.2, U1.31 (GPIO19), U6.1
/~RST_OUT: R12.2, U4.4, U6.10
/~SCSI_ACK: J5.28, J6.38, R16.1, R33.1, U3.3 (A1)
/~SCSI_BSY: J5.26, J6.36, R32.1, U5.8, U5.12
/~SCSI_MSG: J5.30, J6.42, R35.1, U3.12 (B6)
/~SCSI_RST: J5.29, J6.40, R34.1, U6.8, U6.12
/~SCSI_SD0: J5.6, J6.2, R22.1, U2.9 (A7)
/~SCSI_SD1: J5.8, J6.4, R23.1, U2.8 (A6)
/~SCSI_SD2: J5.10, J6.6, R24.1, U2.7 (A5)
/~SCSI_SD3: J5.12, J6.8, R25.1, U2.6 (A4)
/~SCSI_SD4: J5.14, J6.10, R26.1, U2.5 (A3)
/~SCSI_SD5: J5.16, J6.12, R27.1, U2.4 (A2)
/~SCSI_SD6: J5.18, J6.14, R28.1, U2.3 (A1)
/~SCSI_SD7: J5.20, J6.16, R29.1, U2.2 (A0)
/~SCSI_SDP: J5.22, J6.18, R30.1, U5.3, U5.5
/~SCSI_SEL: J5.32, J6.44, R36.1, U6.3, U6.5
/~TERM_EN: Q1.1 (G), Q2.1 (G), Q3.1 (G), Q4.1 (G), Q5.1 (G), Q6.1 (G), Q7.1 (G), Q8.1 (G), Q9.1 (G), Q10.1 (G), Q11.1 (G), Q12.1 (G), Q13.1 (G), Q14.1 (G), Q15.1 (G), Q16.1 (G), Q17.1 (G), Q18.1 (G), R40.2, R43.1, SW1.6
/~USB_BOOT: R53.2, SW1.5
GND: C1.2, C2.2, C3.2, C4.2, C5.2, C6.2, C7.2, C8.2, C9.2, C10.2, C11.2, C12.2, C13.2, C15.2, C16.2, C17.2, C18.2, C19.2, C20.2, C21.2, C22.2, C23.2, C24.2, C25.2, C26.2, C27.2, C28.2, C29.2, C30.2, C31.2, C32.2, C33.2, C34.2, C35.2, C36.2, J1.A1 (GND), J1.A12 (GND), J1.B1 (GND), J1.B12 (GND), J2.6 (GND), J2.CD1, J2.MP1, J2.MP2, J2.MP3, J2.MP4, J4.2, J4.3, J5.3, J5.4, J5.5, J5.7, J5.9, J5.11, J5.13, J5.15, J5.19, J5.21, J5.23, J5.27, J5.31, J5.35, J5.37, J5.38, J6.1, J6.3, J6.5, J6.7, J6.9, J6.11, J6.13, J6.15, J6.17, J6.19, J6.20, J6.21, J6.22, J6.23, J6.24, J6.25, J6.27, J6.28, J6.29, J6.30, J6.31, J6.33, J6.34, J6.35, J6.37, J6.39, J6.41, J6.43, J6.45, J6.47, J6.49, J7.4, R15.2, R42.2, R45.1, R46.2, R47.2, R50.1, R51.2, R52.1, SW1.1, SW1.2, SW1.3, SW1.4, U1.47 (VREG_PGND), U1.61 (GND), U2.10 (GND), U2.19 (CE), U3.9 (A7), U3.10 (GND), U3.11 (B7), U4.3 (GND), U5.4, U5.7 (GND), U5.9, U5.13, U6.2, U6.4, U6.7 (GND), U6.9, U6.13, U8.1 (GND), U9.2 (GND), U10.4 (GND), Y1.2, Y1.4
unnamed: C21.1, R14.2, Y1.1
unnamed: D2.1 (K), JP3.1 (A)
unnamed: D4.2 (A), F1.2, JP3.2 (B)
unnamed: D6.2 (A), U1.37 (GPIO25)
unnamed: D6.1 (K), R52.2
unnamed: F2.1, L1.1
unnamed: C19.1, J1.S1 (SHIELD), R15.1
unnamed: Q1.3 (D), R22.2
unnamed: Q2.3 (D), R23.2
unnamed: Q3.3 (D), R24.2
unnamed: Q4.3 (D), R25.2
unnamed: Q5.3 (D), R26.2
unnamed: Q6.3 (D), R27.2
unnamed: Q7.3 (D), R28.2
unnamed: Q8.3 (D), R29.2
unnamed: Q9.3 (D), R30.2
unnamed: Q10.3 (D), R31.2
unnamed: Q11.3 (D), R32.2
unnamed: Q12.3 (D), R33.2
unnamed: Q13.3 (D), R34.2
unnamed: Q14.3 (D), R35.2
unnamed: Q15.3 (D), R36.2
unnamed: Q16.3 (D), R37.2
unnamed: Q17.3 (D), R38.2
unnamed: Q18.3 (D), R39.2
unnamed: R18.1, U6.11
unnamed: R19.1, U5.6
unnamed: R20.2, U6.6
unnamed: R21.2, U5.11
unnamed: C2.1, R16.2, U3.2 (A0)
unnamed: R17.1, U3.17 (B1)
unnamed: R44.1, R45.2, U7.1 (GND)
unnamed: C14.2, U8.6 (BST)
unnamed: R41.2, R42.1, U8.4 (FB)
unnamed: C14.1, L2.1, U8.2 (SW)

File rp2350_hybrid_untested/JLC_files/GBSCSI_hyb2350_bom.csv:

Designator,Footprint,Quantity,Value,LCSC Part #
"C1, C10, C11, C14, C16, C18, C3, C4, C5, C6, C7",603,11,100nF,C14663
"C12, C13",603,2,22uF,C59461
C15,603,1,10uF,C96446
"C17, C8, C9",603,3,1uF,C15849
C19,402,1,4.7nF,C346200
C2,603,1,12pF,C38523
"C20, C21",402,2,22pF,C1555
"C22, C24, C27, C28, C29, C30, C31, C32, C33, C34",402,10,100nF,C307331
"C23, C25",402,2,1uF,C52923
"C26, C35",402,2,4.7uF,
C36,402,1,100n,
"D1, D6",603,2,YELLOW,C72038
"D2, D3, D4, D5",D_SOD-123,4,D_Schottky,C82544
"F1, F2",805,2,1A,C468888
FID1,Fiducial_0.5mm_Mask1mm,1,Fiducial,N/A
J1,USB_C_Receptacle_HRO_TYPE-C-31-M-12,1,USB_DATA,C165948
J2,TF01A,1,TF003,C5155563 
J3,PinHeader_1x02_P2.54mm_Vertical,1,Conn_01x02,N/A
J4,PinHeader_1x04_P2.54mm_Horizontal,1,Conn_01x04,N/A
J5,PinHeader_2x25-2_P2.00mm_straddle,1,SCSI_50-2P_2mm,N/A
J6,IDC-Header_2x25_P2.54mm_Horizontal,1,SCSI_50P_2.54mm,N/A
J7,PinHeader_1x04_P2.54mm_Vertical,1,Conn_01x04,N/A
JP3,PinHeader_2x01_P2.54mm_Vertical,1,Jumper_2_Open,N/A
L1,603,1,Ferrite_Bead_Small,C1002
L2,L_Vishay_IHLP-2525,1,2.2uH,C540967
L3,1008,1,3.3uH,C222831
"Q1, Q10, Q11, Q12, Q13, Q14, Q15, Q16, Q17, Q18, Q2, Q3, Q4, Q5, Q6, Q7, Q8, Q9",SOT-23,18,AO3401A,C15127
"R1, R10, R11, R12, R13, R18, R2, R3, R40, R43, R5, R54, R7, R8, R9",603,15,4k7,C23162
"R14, R53",402,2,1k,C11702
R15,402,1,1M,C26083
"R16, R22, R23, R24, R25, R26, R27, R28, R29, R30, R31, R32, R33, R34, R35, R36, R37, R38, R39",603,19,110,C22781
"R17, R19, R20, R21, R4, R51, R6",603,7,1k,C21190
R41,603,1,31k6,C25967
R42,603,1,10k,C25804
R45,603,1,0,C21189
"R46, R47",402,2,5k1,C25905
"R48, R49",402,2,27,C25092
"R50, R52",603,2,510,C23193
SW1,SW_DIP_SPSTx04_Slide_6.7x11.72mm_W8.61mm_P2.54mm_LowProfile,1,SW_DIP_x04,C5160841
U1,RP2350-QFN-60-1EP_7x7_P0.4mm_EP3.4x3.4mm_ThermalVias,1,RP2350_60QFN,C9900136995
U10,SOIC-8_5.23x5.23mm_P1.27mm,1,W25Q128JVS,C97521
"U2, U3",SSOP-20_5.3x7.2mm_P0.65mm,2,74LVT245,C2652121
U4,SOT-23-5,1,74AHCT1G125,C12494
"U5, U6",TSSOP-14_4.4x5mm_P0.65mm,2,74LVT125,C7042
U7,SOT-223-3_TabPin2,1,AZ1117-2.85,C14791
U8,TSOT-23-6,1,AP62250WU,C5184228
U9,SOT-23-6,1,USB TVS,C2827654
Y1,Crystal_SMD_3225-4Pin_3.2x2.5mm,1,12MHz,C133334

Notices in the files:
2.5_to_3.5_SCA_carrier_untested/SCA.kicad_pcb:
artwork © grm, 2024
DB25/gbscsi2.kicad_pcb:
CERN OHL-S V2
rp2350_SCA/gbscsi2.kicad_pcb:
artwork © grm, 2025
rp2350_hybrid/gbscsi2.kicad_pcb:
(c)2024 grm
